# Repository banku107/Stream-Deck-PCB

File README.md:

# Stream Deck PCB

A small 4-key USB macro pad, like a mini Elgato Stream Deck, built around a Raspberry Pi Pico.
This was my first PCB, designed in KiCad.

## The board

- 4 MX-style mechanical keys in a 2×2 layout
- 1 LED and 1 330 Ω resistor per key
- Raspberry Pi Pico, which also connects to the computer over USB
- 2-layer board with a ground fill

| Part | Pico pins | Wiring |
|---|---|---|
| Keys SW1–SW4 | GP2–GP5 | Pin → switch → GND (uses the internal pull-ups) |
| LEDs D1–D4 | GP6–GP9 | Pin → 330 Ω → LED → GND |

## Progress

| | |
|---|---|
|  Footprints placed |  Parts arranged, board outline |
|  Final layout |  First traces (SW1, SW2) |
|  All switches routed |  LEDs and resistors started |
|  Most nets routed |  Ground fill, fully routed |

## Ordering the board

Upload [`fabrication/stream-deck-gerbers.zip`](fabrication/stream-deck-gerbers.zip) to JLCPCB (or any
PCB maker). The parts list is in [`bom.csv`](bom.csv).

## Firmware

[`firmware/code.py`](firmware/code.py) runs on CircuitPython and needs the `adafruit_hid` library.
The Pico acts as a USB keyboard: keys 1–4 send F13–F16 and light their LED while held.

## Repository layout

```
hardware/     KiCad project (schematic + PCB)
fabrication/  Gerber + drill files, zipped and unzipped
firmware/     CircuitPython firmware (code.py)
images/       Progress screenshots
bom.csv       Bill of materials
JOURNAL.md    Build log (synced from Half Life)
```

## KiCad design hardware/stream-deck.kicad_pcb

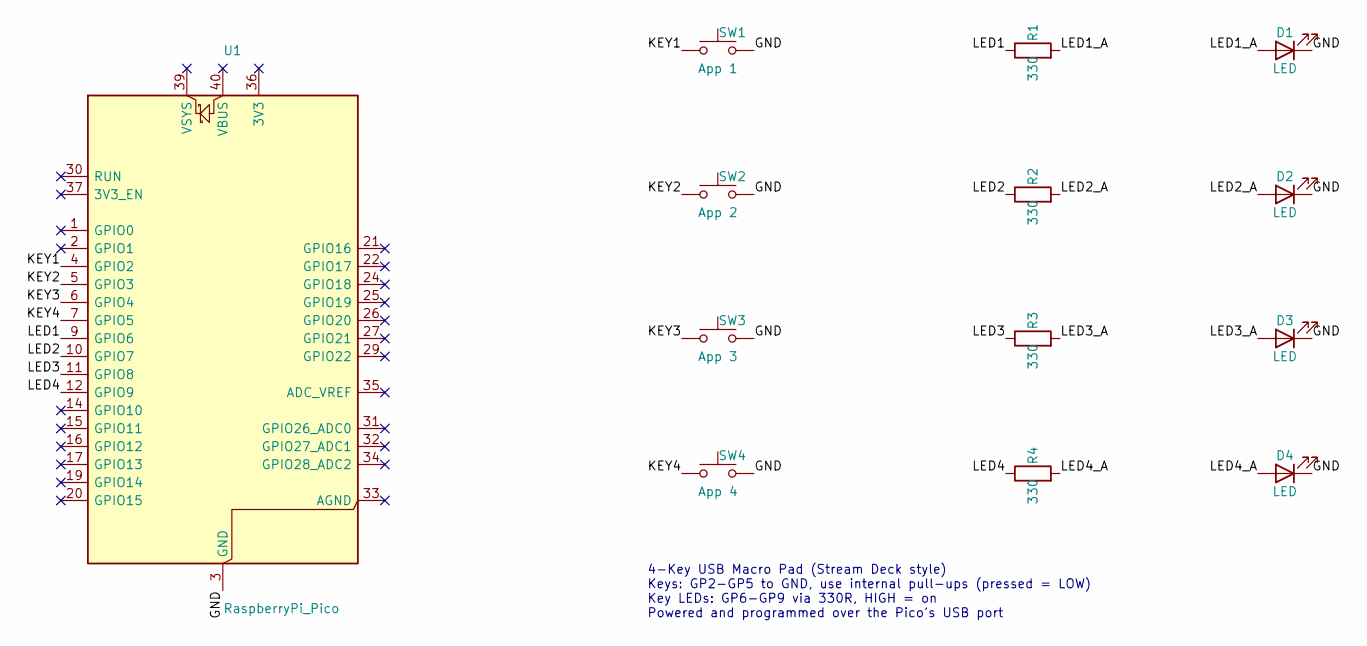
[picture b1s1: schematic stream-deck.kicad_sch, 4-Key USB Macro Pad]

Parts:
D1, D2, D3, D4: LED; LED_D3.0mm
R1, R2, R3, R4: 330; R_Axial_DIN0207_L6.3mm_D2.5mm_P7.62mm_Horizontal
SW1: App 1; SW_Cherry_MX_1.00u_PCB
SW2: App 2; SW_Cherry_MX_1.00u_PCB
SW3: App 3; SW_Cherry_MX_1.00u_PCB
SW4: App 4; SW_Cherry_MX_1.00u_PCB
U1: RaspberryPi_Pico; RaspberryPi_Pico_Common_THT

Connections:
/GND: D1.1 (K), D2.1 (K), D3.1 (K), D4.1 (K), SW1.2, SW2.2, SW3.2, SW4.2, U1.3 (GND), U1.8 (GND), U1.13 (GND), U1.18 (GND), U1.23 (GND), U1.28 (GND), U1.38 (GND)
/KEY1: SW1.1, U1.4 (GPIO2)
/KEY2: SW2.1, U1.5 (GPIO3)
/KEY3: SW3.1, U1.6 (GPIO4)
/KEY4: SW4.1, U1.7 (GPIO5)
/LED1: R1.1, U1.9 (GPIO6)
/LED1_A: D1.2 (A), R1.2
/LED2: R2.1, U1.10 (GPIO7)
/LED2_A: D2.2 (A), R2.2
/LED3: R3.1, U1.11 (GPIO8)
/LED3_A: D3.2 (A), R3.2
/LED4: R4.1, U1.12 (GPIO9)
/LED4_A: D4.2 (A), R4.2

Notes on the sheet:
4-Key USB Macro Pad (Stream Deck style) Keys: GP2-GP5 to GND, use internal pull-ups (pressed = LOW) Key LEDs: GP6-GP9 via 330R, HIGH = on Powered and programmed over the Pico's USB port

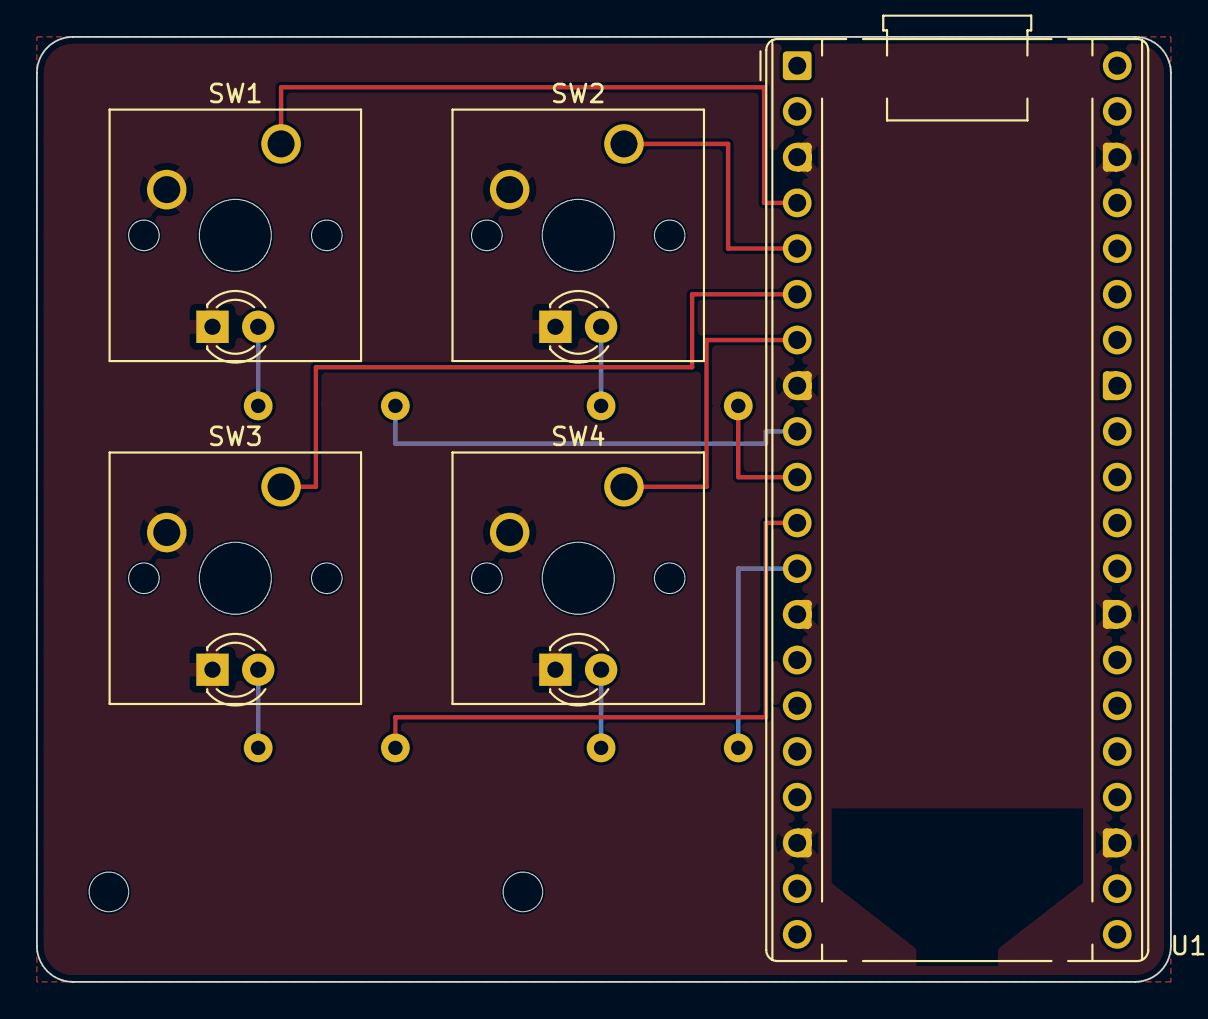
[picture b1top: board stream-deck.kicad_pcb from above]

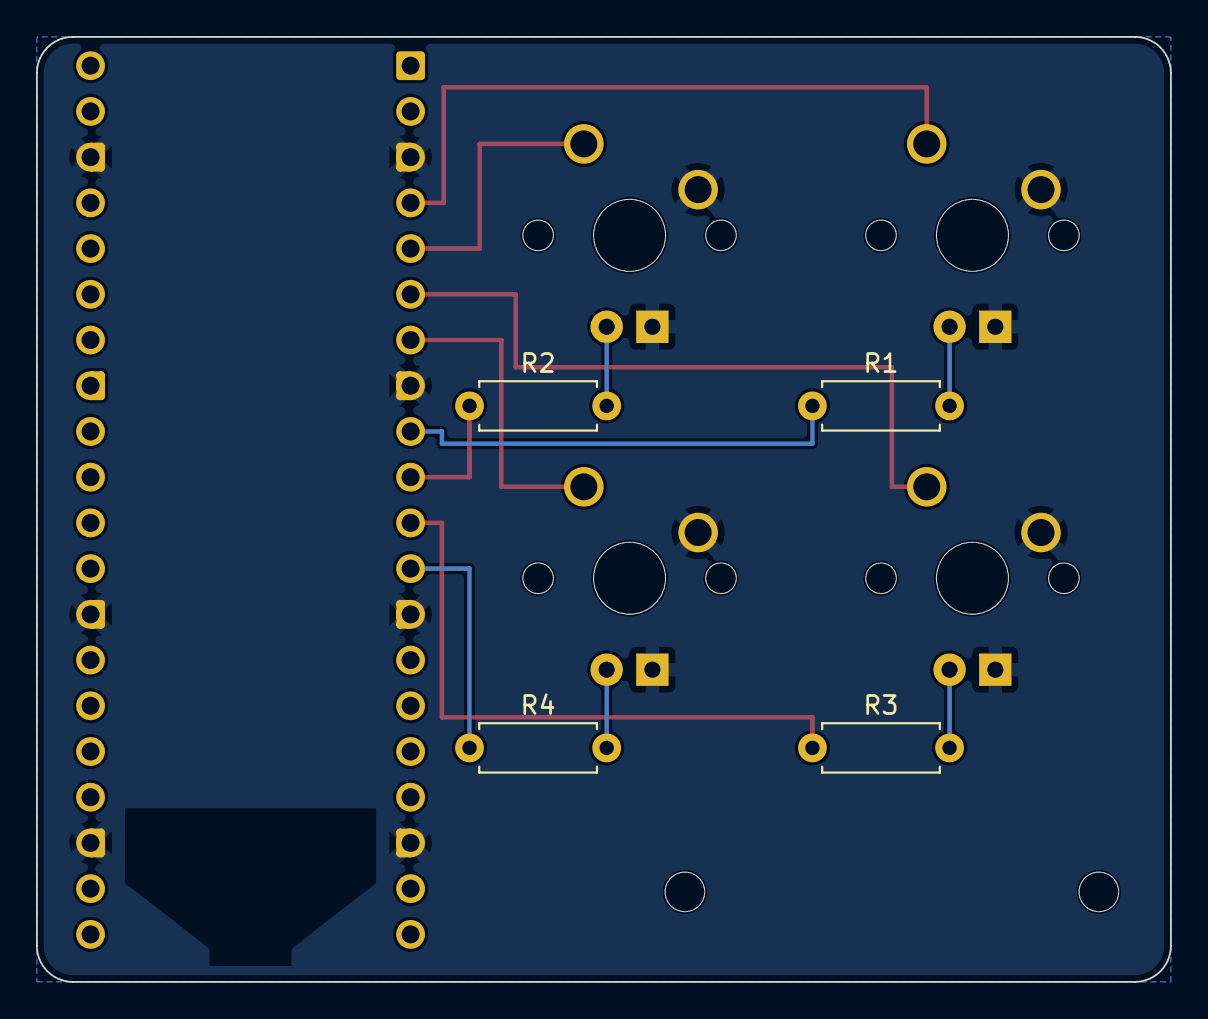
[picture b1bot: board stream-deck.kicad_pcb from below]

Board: 2 copper layers, 63.0 x 52.5 mm, 15 parts (4 on the bottom side), 13 nets.

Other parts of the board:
H1, H2: MountingHole_2.2mm_M2

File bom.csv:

Reference,Qty,Value,Footprint,Description,Source,Unit price (CAD),Notes
U1,1,Raspberry Pi Pico,Module:RaspberryPi_Pico_Common_THT,RP2040 microcontroller board with pre-soldered headers,https://www.amazon.ca/dp/B09X33TBY3,19.95,Freenove; acts as the USB keyboard
SW1 SW2 SW3 SW4,4,Outemu Red (MX-style),Button_Switch_Keyboard:SW_Cherry_MX_1.00u_PCB,"3-pin linear key switch with LED slot (pack of 20)",https://www.amazon.ca/dp/B07TLLT229,16.99,Price is for the 20-pack
-,4,Translucent 1U keycap (OEM R4),-,Frosted translucent blank keycap (pack of 20),https://www.amazon.ca/dp/B0CQ2Y89GQ,17.99,Price is for the 20-pack; translucent so the key LEDs show
D1 D2 D3 D4,4,3 mm LED,LED_THT:LED_D3.0mm,"3 mm round LED, red/yellow/green recommended (pack of 100)",https://www.amazon.ca/dp/B01AUI4W5U,8.99,Optional; sits in each switch's LED slot. Must be 3 mm (5 mm won't fit)
R1 R2 R3 R4,4,330 ohm,Resistor_THT:R_Axial_DIN0207_L6.3mm_D2.5mm_P7.62mm_Horizontal,1/4 W through-hole resistor,From an Arduino kit,0.00,Optional; only needed with the LEDs. 220 ohm also works
H1 H2,2,M2 mounting hole,MountingHole:MountingHole_2.2mm_M2,Mounting hole for a case (part of the PCB),-,0.00,No part to buy
PCB,1,stream-deck PCB,-,"2-layer 63 x 52.5 mm board, 1.6 mm FR4",fabrication/stream-deck-gerbers.zip,-,Order from JLCPCB or similar (min. 5 boards)
